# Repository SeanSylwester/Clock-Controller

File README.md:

# Clock-Controller
Small ATTiny85-based PCB for controlling an old school IBM 3-wire clock

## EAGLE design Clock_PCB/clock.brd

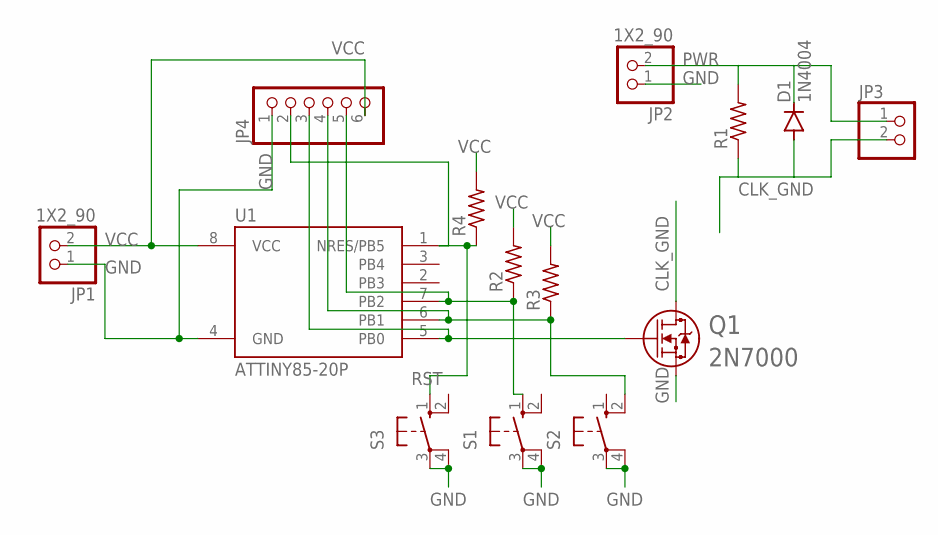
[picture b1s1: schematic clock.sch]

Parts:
D1: 1N4004; DO41-10
JP1, JP2: 1X2_90; 1X02/90
JP3: PINHD-1X2; 1X02
JP4: PINHD-1X6; 1X06
Q1: 2N7000; TO-92
R1, R2, R3, R4: R-US_0204/7; 0204/7
S1, S2, S3: 10-XX; B3F-10XX
U1: ATTINY85-20P; PDIP08_300MIL

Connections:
CLK_GND: D1.A, JP3.2, Q1.3 (2), R1.1
GND: JP1.1, JP2.1, JP4.1, Q1.1 (3), S1.3, S1.4 (P1), S2.3, S2.4 (P1), S3.3, S3.4 (P1), U1.4 (GND)
MISO: JP4.4, R3.1, S2.2 (S1), U1.6 (PB1)
MOSI: JP4.3, Q1.2 (1), U1.5 (PB0)
PWR: D1.C, JP2.2, JP3.1, R1.2
RST: JP4.2, R4.1, S3.1 (S), U1.1 (NRES/PB5)
SCK: JP4.5, R2.1, S1.1 (S), U1.7 (PB2)
VCC: JP1.2, JP4.6, R2.2, R3.2, R4.2, U1.8 (VCC)

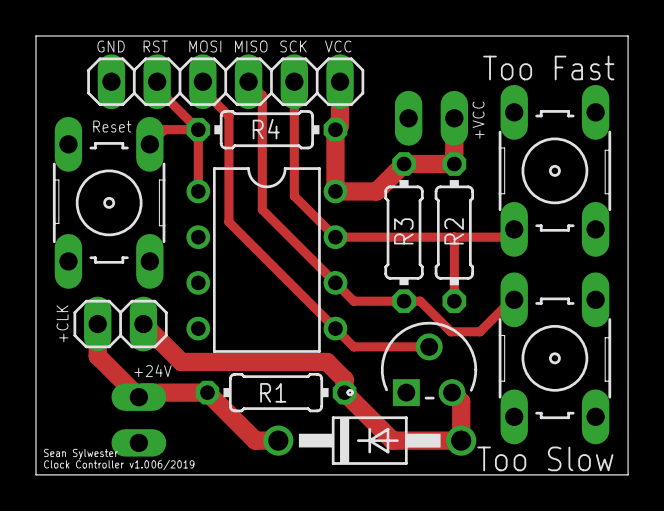
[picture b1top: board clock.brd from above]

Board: 2 copper layers, 32.9 x 24.4 mm, 14 parts (0 on the bottom side), 8 nets.

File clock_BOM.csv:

Quantity,Part Number,Manufacturer Part Number
1,2N7000-G-ND,2N7000-G
2,WM4300-ND,22-05-3021
1,952-2262-ND,M20-9990246
1,2057-PH1-06-UA-ND,PH1-06-UA
1,1N4004RLGOSCT-ND,1N4004RLG
1,ATTINY85-20PU-ND,ATTINY85-20PU
4,10.0KXBK-ND,MFR-25FBF52-10K
3,SW400-ND,B3F-1000

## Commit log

2019-06-08 updated code
2019-06-08 added BOM
